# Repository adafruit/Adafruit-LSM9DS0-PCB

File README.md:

# Adafruit LSM9DS0 PCB (Discontinued)
<a href="http://www.adafruit.com/products/2021"><br/>
Click here to purchase one from the Adafruit shop</a>

When we saw the new LSM9DS0 from ST micro we thought - wow this could really make for a great breakout, at a very nice price! Design your own activity or motion tracker with all the data... We spun up a breakout board that has all the extra circuitry you'll want, like a 3V regulator and level shifting circuitry so it can be used by 3V or 5V power/logic microcontrollers like the Arduino.

PCB files for Adafruit LSM9DS0 9-DOF Sensor PCB. The format is EagleCAD schematic and board layout.
- https://www.adafruit.com/products/2021

### License

Adafruit invests time and resources providing this open source design, please support Adafruit and open-source hardware by purchasing products from [Adafruit](https://www.adafruit.com)!

All text above must be included in any redistribution

Designed by Limor Fried/Ladyada for Adafruit Industries.
Creative Commons Attribution/Share-Alike, all text above must be included in any redistribution. 
See license.txt for additional information.

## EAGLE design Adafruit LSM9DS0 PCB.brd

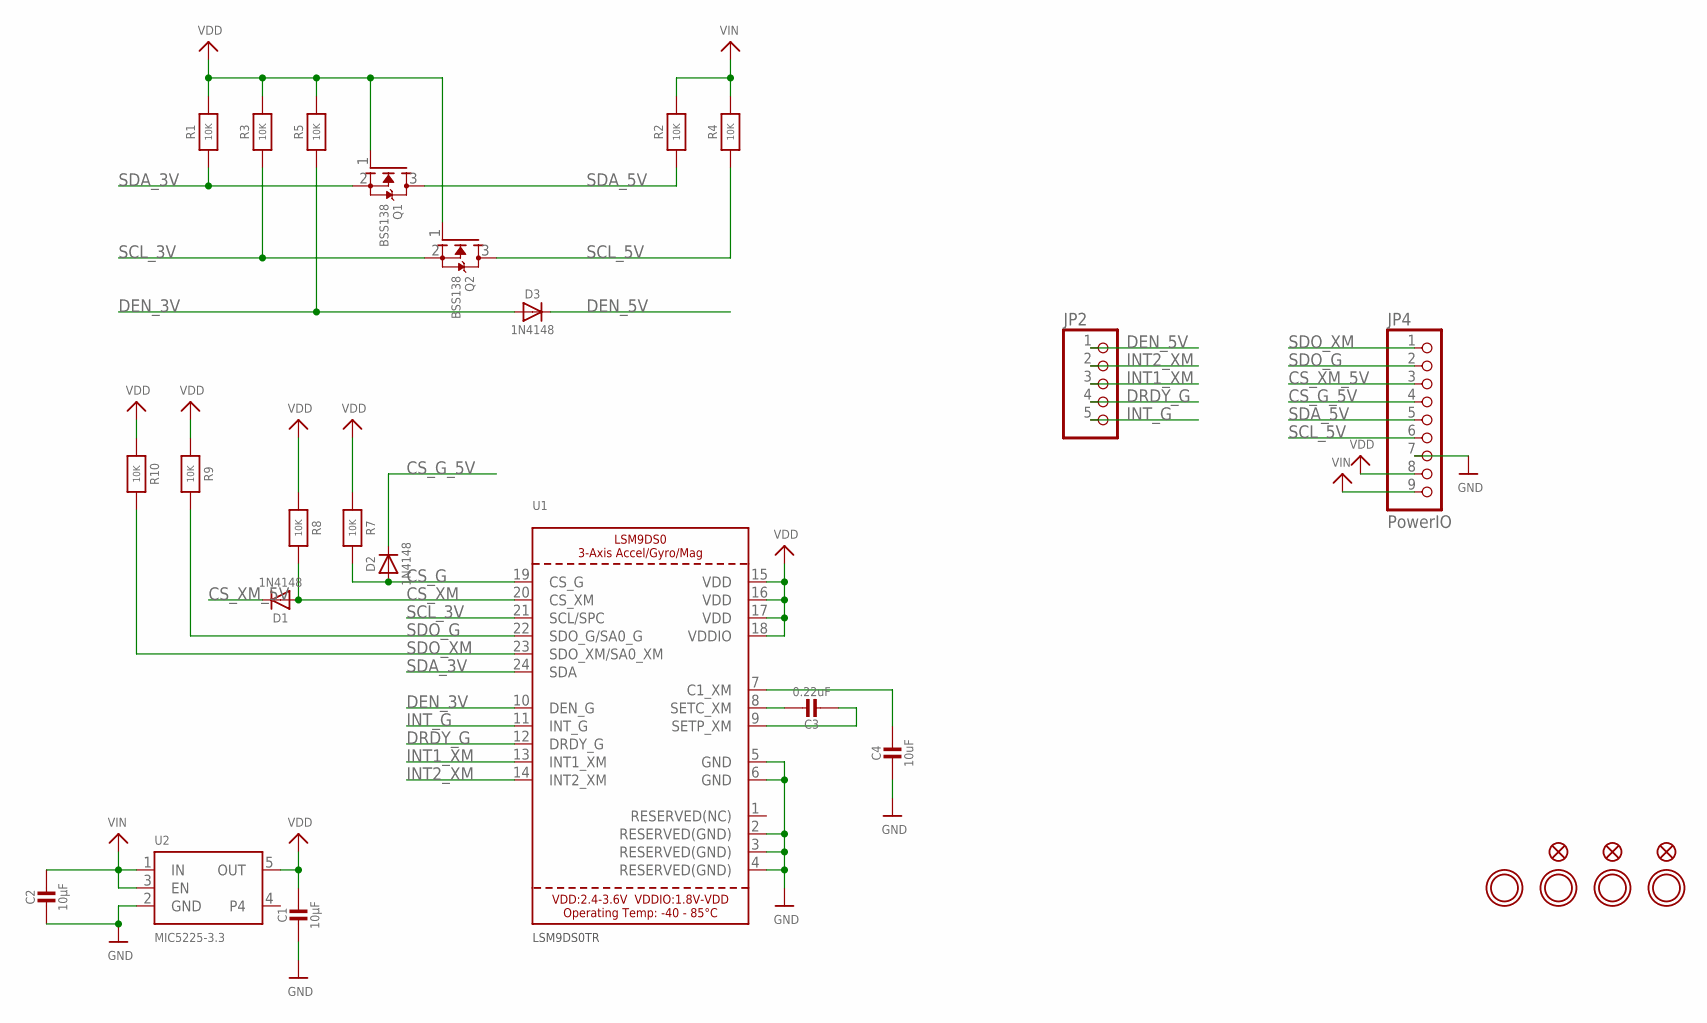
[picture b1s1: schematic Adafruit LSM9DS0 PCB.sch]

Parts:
C1, C2: 10µF; 0805-NO
C3: 0.22uF; 0805-NO
C4: 10uF; 0805-NO
D1, D2, D3: 1N4148; SOD-323
FID1, FID2, FID3: FIDUCIAL""; FIDUCIAL_1MM
JP2: HEADER-1X570MIL; 1X05_ROUND_70
JP4: PowerIO; 1X09_ROUND_70
Q1, Q2: BSS138; SOT23-WIDE
R1, R2, R3, R5, R7, R8, R9, R10: 10K; 0805-NO
R4: 10K; _0805MP
U1: LSM9DS0TR; LGA24_4X4MM
U2: MIC5225-3.3; SOT23-5
U$4, U$5, U$6, U$7: MOUNTINGHOLE2.5; MOUNTINGHOLE_2.5_PLATED

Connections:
CS_G: D2.A, R7.2, U1.19 (CS_G)
CS_G_5V: D2.C, JP4.4
CS_XM: D1.A, R8.2, U1.20 (CS_XM)
CS_XM_5V: D1.C, JP4.3
DEN_3V: D3.A, R5.1, U1.10 (DEN_G)
DEN_5V: D3.C, JP2.1
DRDY_G: JP2.4, U1.12 (DRDY_G)
GND: C1.2, C2.2, C4.2, JP4.7, U1.2 (RESERVED(GND)), U1.3 (RESERVED(GND)), U1.4 (RESERVED(GND)), U1.5 (GND), U1.6 (GND), U2.2 (GND)
INT1_XM: JP2.3, U1.13 (INT1_XM)
INT2_XM: JP2.2, U1.14 (INT2_XM)
INT_G: JP2.5, U1.11 (INT_G)
unnamed: C3.1, U1.8 (SETC_XM)
unnamed: C3.2, U1.9 (SETP_XM)
unnamed: C4.1, U1.7 (C1_XM)
SCL_3V: Q2.2 (S), R3.1, U1.21 (SCL/SPC)
SCL_5V: JP4.6, Q2.3 (D), R4.1
SDA_3V: Q1.2 (S), R1.1, U1.24 (SDA)
SDA_5V: JP4.5, Q1.3 (D), R2.1
SDO_G: JP4.2, R9.2, U1.22 (SDO_G/SA0_G)
SDO_XM: JP4.1, R10.2, U1.23 (SDO_XM/SA0_XM)
VDD: C1.1, JP4.8, Q1.1 (G), Q2.1 (G), R1.2, R3.2, R5.2, R7.1, R8.1, R9.1, R10.1, U1.15 (VDD), U1.16 (VDD), U1.17 (VDD), U1.18 (VDDIO), U2.5 (OUT)
VIN: C2.1, JP4.9, R2.2, R4.2, U2.1 (IN), U2.3 (EN)

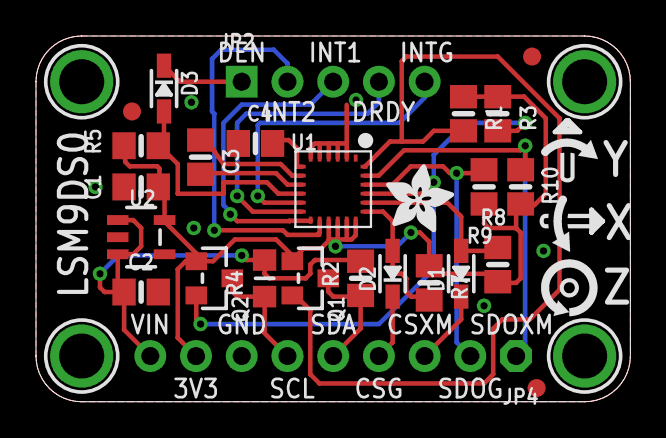
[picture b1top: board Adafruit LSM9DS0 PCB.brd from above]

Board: 2 copper layers, 33.0 x 20.3 mm, 31 parts (0 on the bottom side), 22 nets.

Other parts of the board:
U$14: SYMBOL_GYROXYZ_YREV_10MM
U$23: ADAFRUIT_3.5MM

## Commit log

2015-04-17 init!

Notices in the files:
parts and their libraries:
microbuilder: This work is placed in the public domain, and may be freely used for commercial and non-commercial work with the following conditions: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
